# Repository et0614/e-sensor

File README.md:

# E-Sensor Project

This project provides a complete solution for a MIDI-based sensor device, including hardware design files, microcontroller firmware, and a Python client library.

## Directory Structure

The repository is organized as follows:

```text
.
├── firmware/                # Microcontroller Firmware (MPLAB X IDE)
│   ├── E_Sensor_Main.X/     # Main controller (USB-MIDI & System Logic)
│   └── E_Sensor_Velocity.X/ # Sub-controller (Air velocity sensor processing)
├── hardware/                # Hardware Design Materials
│   ├── pcb/                 # PCB layout and schematics
│   ├── datasheets/          # Technical specifications for key components
│   └── BOM.xlsx             # Bill of Materials
├── software/                # PC-side Applications & Libraries
│   ├── e_sensor.py          # Python client library for E-Sensor
│   └── requirements.txt     # Python dependency list
└── .gitignore               # Git ignore rules for MPLAB X and Python
```

---

## Directory Details

### 1. Firmware (`/firmware`)
Contains MPLAB X IDE projects for the onboard microcontrollers.

* **E_Sensor_Main.X**: 
    * Handles USB-MIDI communication using the TinyUSB stack.
    * Manages system-level logic and MIDI SysEx protocol.
    * Configured via MCC (MPLAB Code Configurator).
* **E_Sensor_Velocity.X**: 
    * Dedicated firmware for the air velocity sensor subunit.
    * Focuses on high-speed signal processing and data filtering.

### 2. Hardware (`/hardware`)
Includes all physical design assets.

* **pcb/**: Original CAD files for the board. A `Schematic.pdf` is provided for quick reference without needing specialized CAD software.
* **datasheets/**: A collection of PDFs for the ICs and sensors used in this design, ensuring all technical references are available offline.

### 3. Software (`/software`)
Tools for interfacing with the device from a computer.

* **e_sensor.py**: 
    * A lightweight Python class that wraps the MIDI SysEx protocol.
    * Supports real-time data polling, device ID retrieval, and coefficient calibration.
* **requirements.txt**: List of necessary Python packages (e.g., `mido`, `python-rtmidi`).

---

## Getting Started

### Firmware Development
* **IDE**: MPLAB X IDE
* **Compiler**: Microchip XC8
* **Plugin**: MCC (MPLAB Code Configurator)

### Python Environment
Install dependencies using pip:
```bash
pip install -r software/requirements.txt
```

---

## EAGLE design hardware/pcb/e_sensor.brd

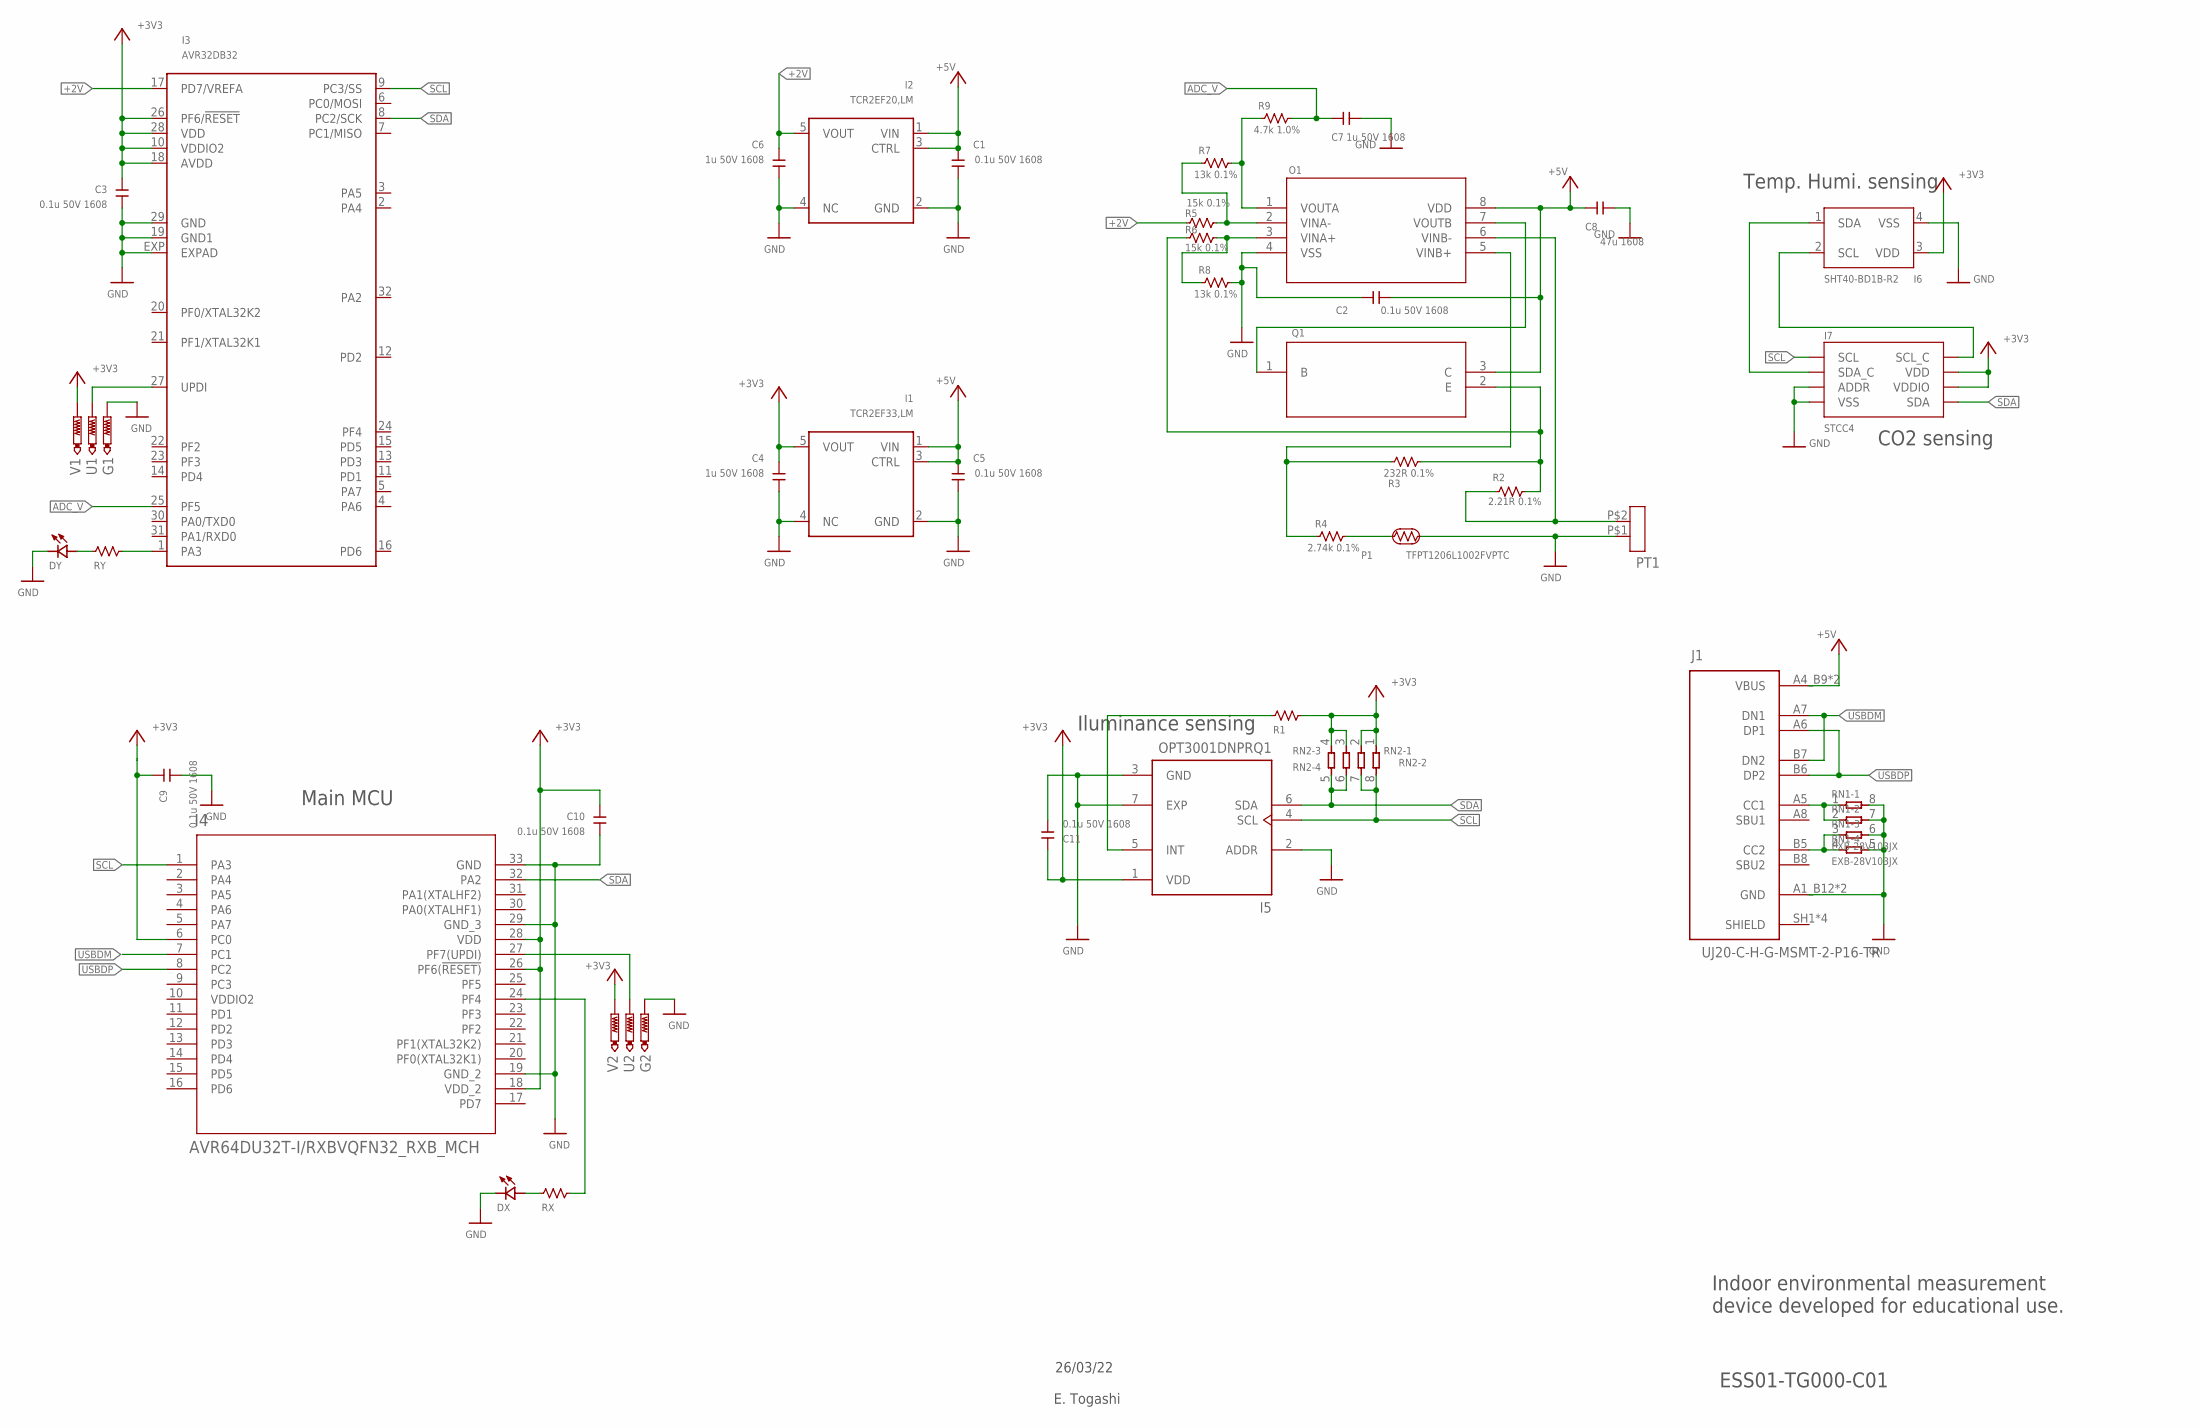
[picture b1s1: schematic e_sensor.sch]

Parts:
C1, C2, C3, C5, C9, C10, C11: 0.1u 50V 1608; C-1608/0603
C4, C6, C7: 1u 50V 1608; C-1608/0603
C8: 47u 1608; C-1608/0603
DX: SML-D12D1WT86; SMD-1608
DY: SML-D12D1WT86; SMD-1608
G1, G2: PTR1B1,27; B1,27
I1: TCR2EF33,LM; SOT23-5L
I2: TCR2EF20,LM; SOT23-5L
I3: AVR32DB32; HVQFN32
I4: AVR64DU32T-I/RXBVQFN32_RXB_MCH; VQFN32_RXB_MCH
I5: OPT3001DNPRQ1; SON65P200X200X65-7N
I6: SHT40-BD1B-R2; SHT41
I7: STCC4
J1: UJ20-C-H-G-MSMT-2-P16-TR; SAMESKY_UJ20-C-H-G-MSMT-2-P16-TR
O1: MCP6V02T-E/MDDFN8_4X4MC_MCH; DFN8_4X4MC_MCH
P1: TFPT1206L1002FVPTC; C1206
PT1: VELHOLE
Q1: MMBT3904-7-FSOT-23_1_DIO; SOT-23_1_DIO
R1: 510R 1608; R-1608/0603
R2: 2.21R 0.1%; R-1608/0603
R3: 232R 0.1%; R-1608/0603
R4: 2.74k 0.1%; R-1608/0603
R5, R6: 15k 0.1%; R-1608/0603
R7, R8: 13k 0.1%; R-1608/0603
R9: 4.7k 1.0%; R-1608/0603
RN1, RN2: EXB-28V103JX; RESCAXS50P200X100X45-8N
RX: 510R 1608; R-1608/0603
RY: 510R 1608; R-1608/0603
U1, U2: PTR1B1,27; B1,27
V1, V2: PTR1B1,27; B1,27

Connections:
+2V: C6.P$1 (1), I2.5 (VOUT), I3.17 (PD7/VREFA), R5.1
+3V3: C3.P$1 (1), C4.P$1 (1), C9.P$1 (1), C10.P$1 (1), C11.P$1 (1), I1.5 (VOUT), I3.10 (VDDIO2), I3.18 (AVDD), I3.26 (PF6/!RESET), I3.28 (VDD), I4.6 (PC0), I4.18 (VDD_2), I4.26 (PF6(!RESET)), I4.28 (VDD), I5.1 (VDD), I6.3 (VDD), I7.VDD, I7.VDDIO, R1.2, RN2.1, RN2.2 (1), RN2.3 (1), RN2.4 (1), V1.TP, V2.TP
+5V: C1.P$1 (1), C2.P$1 (1), C5.P$1 (1), C8.P$1 (1), I1.1 (VIN), I1.3 (CTRL), I2.1 (VIN), I2.3 (CTRL), J1.A4_B9 (VBUS), J1.B4_A9 (VBUS), O1.8 (VDD), Q1.3 (C)
ADC_V: C7.P$1 (1), I3.25 (PF5), R9.2
GND: C1.P$2 (2), C2.P$2 (2), C3.P$2 (2), C4.P$2 (2), C5.P$2 (2), C6.P$2 (2), C7.P$2 (2), C8.P$2 (2), C9.P$2 (2), C10.P$2 (2), C11.P$2 (2), DX.2 (C), DY.2 (C), G1.TP, G2.TP, I1.2 (GND), I1.4 (NC), I2.2 (GND), I2.4 (NC), I3.19 (GND1), I3.29 (GND), I3.EXP (EXPAD), I4.19 (GND_2), I4.29 (GND_3), I4.33 (GND), I5.2 (ADDR), I5.3 (GND), I5.7 (EXP), I6.4 (VSS), I7.ADDR, I7.VSS, J1.A1_B12 (GND), J1.B1_A12 (GND), O1.4 (VSS), P1.1, PT1.P$1, R8.2, RN1.5 (2), RN1.6 (2), RN1.7 (2), RN1.8 (2)
unnamed: I4.24 (PF4), RX.2
unnamed: DY.1 (A), RY.1
unnamed: O1.1 (VOUTA), R7.2, R9.1
unnamed: DX.1 (A), RX.1
unnamed: O1.5 (VINB+), R3.1, R4.1
unnamed: I3.1 (PA3), RY.2
unnamed: J1.A5 (CC1), RN1.1, RN1.2 (1)
unnamed: J1.B5 (CC2), RN1.3 (1), RN1.4 (1)
unnamed: I5.5 (INT), R1.1
unnamed: Q1.2 (E), R2.2, R3.2, R6.1
unnamed: O1.7 (VOUTB), Q1.1 (B)
unnamed: O1.3 (VINA+), R6.2, R8.1
unnamed: O1.2 (VINA-), R5.2, R7.1
PT1: O1.6 (VINB-), PT1.P$2, R2.1
PTC1: P1.2, R4.2
SCL: I3.9 (PC3/SS), I4.1 (PA3), I5.4 (SCL), I7.SCL, RN2.7 (2), RN2.8 (2)
SCL_C: I6.2 (SCL), I7.SCL_C
SDA: I3.8 (PC2/SCK), I4.32 (PA2), I5.6 (SDA), I7.SDA, RN2.5 (2), RN2.6 (2)
SDA_C: I6.1 (SDA), I7.SDA_C
UPDI1: I3.27 (UPDI), U1.TP
UPDI2: I4.27 (PF7(UPDI)), U2.TP
USBDM: I4.7 (PC1), J1.A7 (DN1), J1.B7 (DN2)
USBDP: I4.8 (PC2), J1.A6 (DP1), J1.B6 (DP2)
VDDIO2: I4.10 (VDDIO2)

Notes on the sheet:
Indoor environmental measurement device developed for educational use.
ESS01-TG000-C01
E. Togashi
26/03/22
Main MCU
Iluminance sensing
Temp. Humi. sensing
CO2 sensing

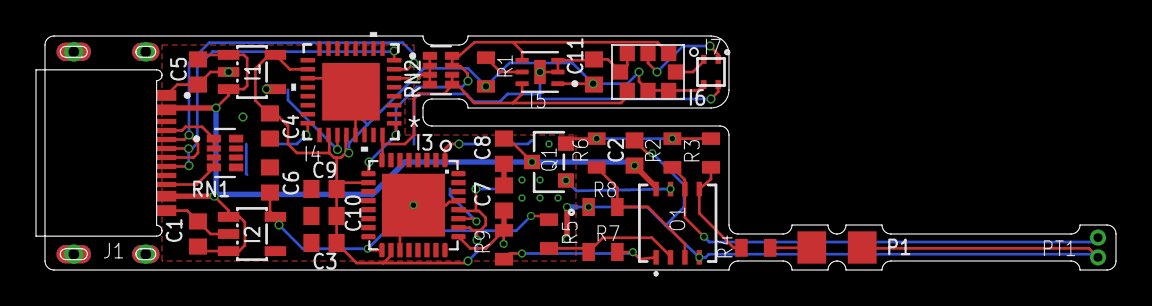
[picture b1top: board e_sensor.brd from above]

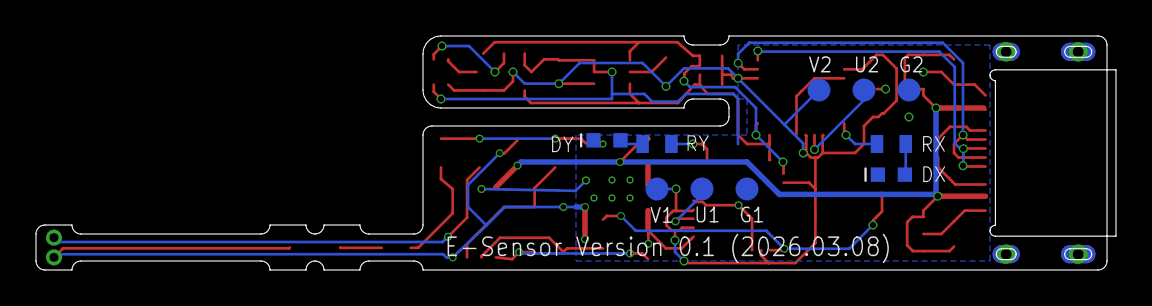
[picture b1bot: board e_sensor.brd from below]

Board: 2 copper layers, 59.5 x 13.0 mm, 44 parts (10 on the bottom side), 28 nets.

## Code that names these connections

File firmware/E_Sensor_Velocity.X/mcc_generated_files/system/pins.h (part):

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
/**
 * @ingroup  pinsdriver
 * @brief Default Interrupt Handler for IO_PC3 pin. 
 *        This is a predefined interrupt handler to be used together with the IO_PC3_SetInterruptHandler() method.
 *        This handler is called every time the IO_PC3 ISR is executed. 
 * @pre PIN_MANAGER_Initialize() has been called at least once
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
/**
 * @ingroup  pinsdriver
 * @brief Interrupt Handler Setter for IO_PC3 pin input-sense-config functionality.
 *        Allows selecting an interrupt handler for IO_PC3 at application runtime
 * @pre PIN_MANAGER_Initialize() has been called at least once
 * @param InterruptHandler function pointer.
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
/**
 * @ingroup  pinsdriver
 * @brief Default Interrupt Handler for IO_PC2 pin. 
 *        This is a predefined interrupt handler to be used together with the IO_PC2_SetInterruptHandler() method.
 *        This handler is called every time the IO_PC2 ISR is executed. 
 * @pre PIN_MANAGER_Initialize() has been called at least once
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
/**
 * @ingroup  pinsdriver
 * @brief Interrupt Handler Setter for IO_PC2 pin input-sense-config functionality.
 *        Allows selecting an interrupt handler for IO_PC2 at application runtime
 * @pre PIN_MANAGER_Initialize() has been called at least once
 * @param InterruptHandler function pointer.
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
/**
 * @ingroup  pinsdriver
 * @brief Default Interrupt Handler for IO_PF5 pin. 
 *        This is a predefined interrupt handler to be used together with the IO_PF5_SetInterruptHandler() method.
 *        This handler is called every time the IO_PF5 ISR is executed. 
 * @pre PIN_MANAGER_Initialize() has been called at least once
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
/**
 * @ingroup  pinsdriver
 * @brief Interrupt Handler Setter for IO_PF5 pin input-sense-config functionality.
 *        Allows selecting an interrupt handler for IO_PF5 at application runtime
 * @pre PIN_MANAGER_Initialize() has been called at least once
 * @param InterruptHandler function pointer.
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
/**
 * @ingroup  pinsdriver
 * @brief Default Interrupt Handler for IO_PF4 pin. 
 *        This is a predefined interrupt handler to be used together with the IO_PF4_SetInterruptHandler() method.
 *        This handler is called every time the IO_PF4 ISR is executed. 
 * @pre PIN_MANAGER_Initialize() has been called at least once
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
/**
 * @ingroup  pinsdriver
 * @brief Interrupt Handler Setter for IO_PF4 pin input-sense-config functionality.
 *        Allows selecting an interrupt handler for IO_PF4 at application runtime
 * @pre PIN_MANAGER_Initialize() has been called at least once
 * @param InterruptHandler function pointer.
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
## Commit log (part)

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2026-03-20 Initial commit.
2026-03-21 要求時のみ計測データ送信とする方式に変更。
2026-03-22 CO2センサ初期化処理を追加
2026-03-23 CO2初期校正のため、初回起動時の処理を追加。
2026-04-19 CO2の初期調整処理用コマンドを追加。 起動時の自動初期調整を削除。
2026-04-19 Main FW の堅牢化 (Phase 1): WDT / I2C・EEPROM タイムアウト / SysEx 状態機械 / 32bitタイマのアトミック化
    - main.c: WDT (~4s) を有効化し、main ループで wdt_reset() を呼ぶ。
    sec_timer / co2_pfm_timer の読み書きを ATOMIC_BLOCK でアトミック化。
    初期調整完了後の連続計測開始が失敗した場合に I2C を叩き続けないよう 1sec
    バックオフを追加。
    - i2c_master.c: 完了待ちにループカウンタ式タイムアウトを追加し、タイムアウト
    時は TWI0 を再初期化してバスを強制復帰させる。
2026-04-19 Main FW 仕様整合 (Phase 2): stcc4 includeの修正 / 係数検証 / CO2校正の符号 / コメント整理
    - stcc4.c: #include "Stcc4.h" を "stcc4.h" に修正（Linux/macOS での大文字小文字
    によるビルド不能バグ）。
    - stcc4.c: STCC4_initialize() がジェネラルコールの I2C 失敗を握り潰して常に
    true を返していたので、戻り値を伝搬するよう修正。
    - midi_app.c: CMD_COEF_A_DATA / CMD_COEF_B_DATA で受信した係数を
    (float*)decoded のキャストで直接渡していたのを memcpy 経由に変更し、
2026-04-20 Python クライアント: CO2 初期調整コマンド対応 + 付随修正
    - CO2 初期調整系 3 コマンドのサポートを追加
    - CMD_CONDITIONING_REQ (0x17) H->D
    - CMD_CONDITIONING_START (0x18) D->H
    - CMD_CONDITIONING_DONE (0x19) D->H
    上記 3 定数、送信メソッド request_conditioning()、および
    開始〜完了までブロック待機する同期 API perform_conditioning(
2026-04-20 MAUIプロジェクト追加前処理。
2026-04-20 MAUIプロジェクト追加。
2026-04-23 Autodesk Fusionに対応 一部部品の入れ替え
2026-04-23 MAUI プロジェクトの階層をフラット化 (E-Sensor_vs/ を削除)
    software/maui/E-Sensor_vs/{E-Sensor.slnx, E-Sensor/} を 1 階層上げて
    software/maui/{E-Sensor.slnx, E-Sensor/} に変更。「_vs」サフィックスは
    MAUI である時点で VS 想定が自明なため冗長で、software/python/ と
    対称性を持たせる意味でもフラットなほうが自然なので整理した。
    .slnx 内のプロジェクト参照は相対パス (E-Sensor/E-Sensor.csproj) の
    ままなので、ソリューションを開き直せばビルドはそのまま通る。
2026-04-23 PropertyGroupを整理。
2026-04-23 MAUI: MacCatalyst の DI 登録修正 + CMD_START_MEAS 送信の一元化
    ## MacCatalyst の DI 登録
    - 以前は MauiProgram.cs に #if WINDOWS / ANDROID / IOS の分岐しか無く、
    MacCatalyst ターゲットでは IMidiService / ILoggingService が DI に
    登録されず起動時クラッシュしていた。
    - MacCatalyst は iOS と同じ CoreMIDI / UIKit / AVFoundation を持つため、
    csproj 側に条件付き Compile Include を追加して Platforms\iOS\ 配下の
2026-04-23 MAUI: csproj の重複 Compile 指定を撤回
    MAUI SDK は Platforms/iOS/ 配下を MacCatalyst ターゲットでも既定で
    コンパイル対象にしているため、先行コミットで追加した csproj の
    Compile Include は重複指定となり NETSDK1022 相当のエラーになる。
    ItemGroup を撤回し、MauiProgram.cs の #elif IOS || MACCATALYST 分岐
    だけで MacCatalyst DI 問題を解消する形に修正した。MauiProgram.cs の
    コメントも実態に合わせて更新。
2026-04-23 MAUI: csproj の重複 Compile 指定を撤回 (MacCatalyst ビルドエラー修正)
    PR #5 で導入した csproj の以下 ItemGroup は、MAUI SDK が MacCatalyst
    ビルド時に Platforms/iOS/ 配下を既定で Compile 対象にするため重複指定
    となり、NETSDK1022 エラーでビルドが通らなかった。
    <ItemGroup Condition="... == 'maccatalyst'">
    <Compile Include="Platforms\iOS\IosMidiService.cs" />
    <Compile Include="Platforms\iOS\IosLoggingService.cs" />
2026-04-23 MAUI: CO2 初期調整 / 工場出荷時リセット用のメンテナンスメニューを追加
    CO2 センサの「初期調整 (CMD_CONDITIONING_REQ = 0x17)」と「工場出荷時
    リセット (CMD_CO2_RESET_REQ = 0x15)」を MAUI から実行できるようにする。
    誤操作防止のため、ロギング開始ボタンとは並べず、左サイドバー右下の
    VER/ID 表示の左に小さな歯車アイコン (ImageButton) を 1 つ配置し、
    タップで ActionSheet を開いて操作を選ぶ 3 段階フロー (アイコン →
    ActionSheet → 確認ダイアログ) とした。
2026-04-23 MAUI: メンテナンスメニューのフィードバック反映
    - ConfirmConditioningMsg: 初期調整中は CO2 だけでなく温度・湿度も
    読み取り不可になる旨を追記（英日両方）。
    - 工場出荷時リセット: 破壊的ではなく、校正データを消すわけではなく
    過去トレンドから自動校正し直すだけなので、二段階確認（RESET 入力
    の DisplayPromptAsync）を通常の Yes/No の DisplayAlertAsync に簡略化。
    ActionSheet 表示ラベルから「破壊的」の注記も削除。メッセージ本文も
2026-04-23 MAUI: メンテナンスボタンの最小サイズ制約を解除
    Resources/Styles/Styles.xaml の ImageButton グローバル Style が
    Material Design の最小タップ領域として MinimumHeightRequest=44 /
    MinimumWidthRequest=44 を強制していたため、WidthRequest=9 が効かず
    アイコンが 44dp のまま表示されていた。
    インスタンス側で MinimumWidthRequest=0 / MinimumHeightRequest=0 を
    明示し、9x9 が反映されるようにした。
2026-04-23 アイコンサイズ調整
2026-04-23 Main FW: 起動直後の CMD_CONDITIONING_DONE 誤発火を修正
    co2_pfm_timer の初期値が 0 だったため、sei() 後の 1msec ISR が
    "if (0 <= co2_pfm_timer) co2_pfm_timer++;" の条件でブート直後から
    カウントを始めてしまい、起動から約 23 秒後に
    "if (23000 < co2_pfm_timer)" 分岐が成立して
    CMD_CONDITIONING_DONE を勝手に送信していた（ユーザー側 MAUI
    アプリで「CO2 初期調整が完了した」メッセージが毎回表示される
2026-04-23 MAUI iOS: 画面向きをポートレート(正立・上下反転)のみに制限
    - iPhone (UISupportedInterfaceOrientations): 縦向きのみだった所に
    PortraitUpsideDown を追加して上下反転時にも回転できるように。
    - iPad (UISupportedInterfaceOrientations~ipad): LandscapeLeft /
    LandscapeRight を削除して横向きをサポート対象外に。縦向き 2 つ
    (Portrait / PortraitUpsideDown) のみに統一。
    Android 側は Platforms/Android/MainActivity.cs で既に
2026-04-29 MAUI: メンテナンスアイコンを ImageButton から Image+TapGestureRecognizer に変更
    iOS の MAUI ImageButton は、小サイズ + BackgroundColor=Transparent +
    Padding=0 の組合せで内部の UIButton.imageView が正しく描画されない
    既知の癖がある（タップ判定は ImageButton 枠が機能するためタップ自体
    は通る）。Android で動いていたものが iOS で「タップは反応するけれど
    歯車アイコンは見えない」状態になっていた。
    Image + TapGestureRecognizer に置換し、CanExecute は IsDeviceConnected
2026-04-29 MAUI iOS: maintenance.svg のラスタライズ問題を修正
    実機 (iPhone) 起動時のログに以下の警告が出ており、画像ファイル
    そのものが iOS バンドル内で見つからない (= Resizetizer が
    ラスタライズに失敗したか、glob でアイテムとして拾えていない)
    状態だった:
    Microsoft.Maui.FileImageSourceService: Warning:
    Unable to load image file 'maintenance.svg'.
2026-04-29 MAUI iOS: 歯車アイコンを SVG → PNG (192x192) に置換
    PR #10 の SVG 改修と csproj BaseSize 追加でも iOS で
    "Microsoft.Maui.FileImageSourceService: Warning: Unable to load
    image file 'maintenance.svg'." の警告が継続して出ており、
    Resizetizer の SVG ラスタライズパス自体が iOS で機能して
    いないことが確認できた。
    SVG をやめて、cairosvg で事前に 192x192 RGBA の PNG として
2026-04-29 MAUI iOS: UIRequiresFullScreen=true で iPad multitasking から opt out
    Apple Transporter のバリデーション (409) で以下のエラーが出ていた:
    Invalid bundle. The "Portrait,PortraitUpsideDown" orientations
    were provided ... but you need to include all of the
    "Portrait,PortraitUpsideDown,LandscapeLeft,LandscapeRight"
    orientations to support iPad multitasking.
    Apple のルール: iPad アプリで multitasking (Slide Over /
2026-04-29 バージョン更新。Commonフォルダへの参照削除
2026-05-14 2026.05.14発注版
2026-05-16 風速校正データ表示機能の追加
2026-06-01 プログラマ変更、BOMのミス修正（コンデンサ容量））
2026-06-04 バージョン更新。
2026-06-23 hardware更新（風速On/Off回路）

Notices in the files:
parts and their libraries:
COPYRIGHT: Copyright (C) 2025 Ultra Librarian. All rights reserved.
